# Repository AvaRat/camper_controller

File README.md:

# Camper Controller

## Overview
The project aims to create a usable system that can be mounted in a campervan, trailer, 4x4 overland vehicle or even small boat. It might be usefull in setups where 12V installation is present.
High level system design is presented in [system design doc](<CamperVan Control Unit system design.pdf>) .

## How to interpret this repo
Project contains electronic parts as well as control logic and user interface source codes. I decided to keep everything in one repo as all parts are pretty much dependent on each other, and with this being one-person project keeping all parts in one place make perfect sense to me.

Please see [design decisions.md](design_decisions.md) for details regarding some of the decision made.

## Roadmap
One of the gratest inspirations for me regarding how to organise things is the Opulo project: [opulo](https://github.com/opulo-inc/lumenpnp/tree/main) I'm still far away from it, but that's something I'm aiming for with respect to project structure and organisation.

Ideally I would like to use github pipelines to create BOM from PCB design files. Also somehow linking pin assignment from Kicad into C code would be great. 

Besides, the project is still in the early phase and requires some time to bring it to working prototype phase.

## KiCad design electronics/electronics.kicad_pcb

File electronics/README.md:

# Electronics for Camper Controller

TODO

image

short description

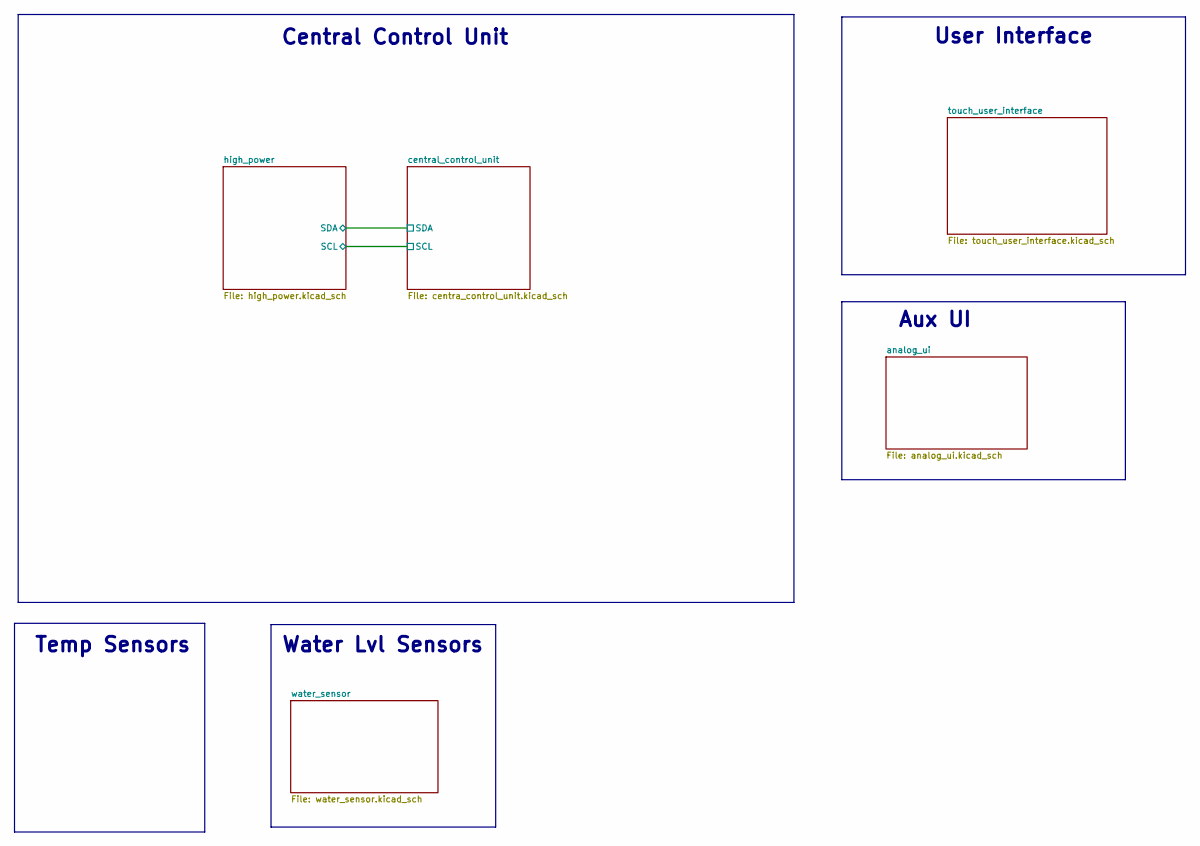
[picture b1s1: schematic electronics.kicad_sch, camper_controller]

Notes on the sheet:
User Interface
Central Control Unit
Temp Sensors
Water Lvl Sensors
Aux UI

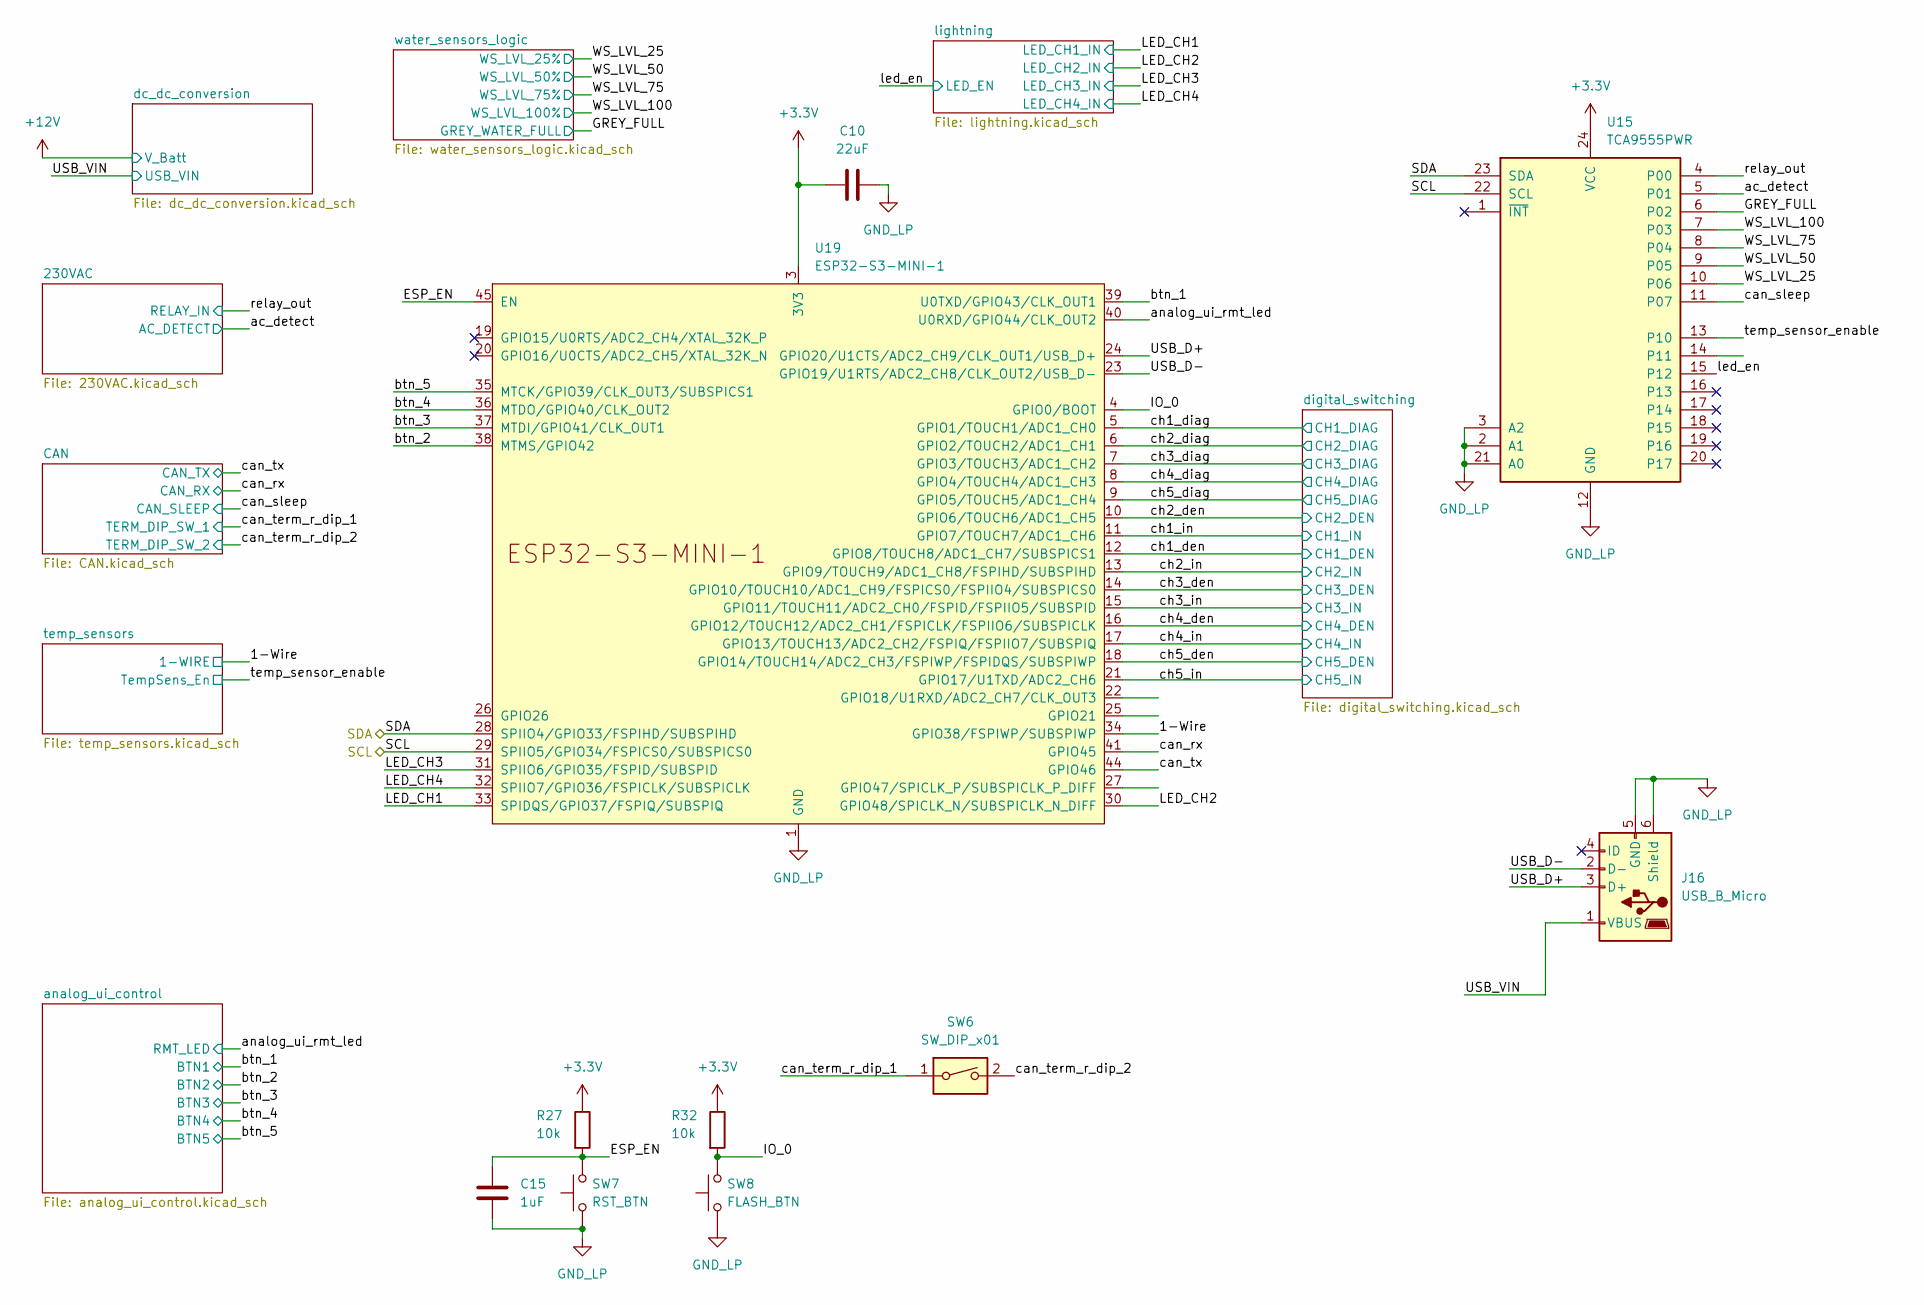
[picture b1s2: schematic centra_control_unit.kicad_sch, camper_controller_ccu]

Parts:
C10: 22uF; C_0805_2012Metric
C15: 1uF; C_0805_2012Metric
J16: USB_B_Micro; USB_Micro-B_Wuerth_614105150721_Vertical; LCSC C2926997
R27, R32: 10k; R_0805_2012Metric
SW6: SW_DIP_x01; PinHeader_1x02_P1.00mm_Vertical
SW7: RST_BTN; SW_PUSH_6mm_H4.3mm
SW8: FLASH_BTN; SW_PUSH_6mm_H4.3mm
U15: TCA9555PWR; TSSOP-24_4.4x7.8mm_P0.65mm; LCSC C465732
U19: ESP32-S3-MINI-1; ESP32-S3-MINI-1U

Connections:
+3.3V: C10.2, R27.1, R32.1, U15.24 (VCC), U19.3 (3V3); also elsewhere on the board
/central_control_unit/1-Wire: U19.34 (GPIO38/FSPIWP/SUBSPIWP); also elsewhere on the board
/central_control_unit/ESP_EN: C15.1, R27.2, SW7.2, U19.45 (EN)
/central_control_unit/GREY_FULL: U15.6 (P02); also elsewhere on the board
/central_control_unit/IO_0: R32.2, SW8.2, U19.4 (GPIO0/BOOT)
/central_control_unit/LED_CH1: U19.33 (SPIDQS/GPIO37/FSPIQ/SUBSPIQ); also elsewhere on the board
/central_control_unit/LED_CH2: U19.30 (GPIO48/SPICLK_N/SUBSPICLK_N_DIFF); also elsewhere on the board
/central_control_unit/LED_CH3: U19.31 (SPIIO6/GPIO35/FSPID/SUBSPID); also elsewhere on the board
/central_control_unit/LED_CH4: U19.32 (SPIIO7/GPIO36/FSPICLK/SUBSPICLK); also elsewhere on the board
/central_control_unit/SCL: U15.22 (SCL), U19.29 (SPIIO5/GPIO34/FSPICS0/SUBSPICS0); also elsewhere on the board
/central_control_unit/SDA: U15.23 (SDA), U19.28 (SPIIO4/GPIO33/FSPIHD/SUBSPIHD); also elsewhere on the board
/central_control_unit/USB_D+: J16.3 (D+), U19.24 (GPIO20/U1CTS/ADC2_CH9/CLK_OUT1/USB_D+)
/central_control_unit/USB_D-: J16.2 (D-), U19.23 (GPIO19/U1RTS/ADC2_CH8/CLK_OUT2/USB_D-)
/central_control_unit/USB_VIN: J16.1 (VBUS); also elsewhere on the board
/central_control_unit/WS_LVL_25: U15.10 (P06); also elsewhere on the board
/central_control_unit/WS_LVL_50: U15.9 (P05); also elsewhere on the board
/central_control_unit/WS_LVL_75: U15.8 (P04); also elsewhere on the board
/central_control_unit/WS_LVL_100: U15.7 (P03); also elsewhere on the board
/central_control_unit/ac_detect: U15.5 (P01); also elsewhere on the board
/central_control_unit/analog_ui_rmt_led: U19.40 (U0RXD/GPIO44/CLK_OUT2); also elsewhere on the board
/central_control_unit/btn_1: U19.39 (U0TXD/GPIO43/CLK_OUT1); also elsewhere on the board
/central_control_unit/btn_2: U19.38 (MTMS/GPIO42); also elsewhere on the board
/central_control_unit/btn_3: U19.37 (MTDI/GPIO41/CLK_OUT1); also elsewhere on the board
/central_control_unit/btn_4: U19.36 (MTDO/GPIO40/CLK_OUT2); also elsewhere on the board
/central_control_unit/btn_5: U19.35 (MTCK/GPIO39/CLK_OUT3/SUBSPICS1); also elsewhere on the board
/central_control_unit/can_rx: U19.41 (GPIO45); also elsewhere on the board
/central_control_unit/can_sleep: U15.11 (P07); also elsewhere on the board
/central_control_unit/can_term_r_dip_1: SW6.1; also elsewhere on the board
/central_control_unit/can_term_r_dip_2: SW6.2; also elsewhere on the board
/central_control_unit/can_tx: U19.44 (GPIO46); also elsewhere on the board
/central_control_unit/ch1_den: U19.12 (GPIO8/TOUCH8/ADC1_CH7/SUBSPICS1); also elsewhere on the board
/central_control_unit/ch1_diag: U19.5 (GPIO1/TOUCH1/ADC1_CH0); also elsewhere on the board
/central_control_unit/ch1_in: U19.11 (GPIO7/TOUCH7/ADC1_CH6); also elsewhere on the board
/central_control_unit/ch2_den: U19.10 (GPIO6/TOUCH6/ADC1_CH5); also elsewhere on the board
/central_control_unit/ch2_diag: U19.6 (GPIO2/TOUCH2/ADC1_CH1); also elsewhere on the board
/central_control_unit/ch2_in: U19.13 (GPIO9/TOUCH9/ADC1_CH8/FSPIHD/SUBSPIHD); also elsewhere on the board
/central_control_unit/ch3_den: U19.14 (GPIO10/TOUCH10/ADC1_CH9/FSPICS0/FSPIIO4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); also elsewhere on the board
/central_control_unit/ch3_diag: U19.7 (GPIO3/TOUCH3/ADC1_CH2); also elsewhere on the board
/central_control_unit/ch3_in: U19.15 (GPIO11/TOUCH11/ADC2_CH0/FSPID/FSPIIO5/S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); also elsewhere on the board
/central_control_unit/ch4_den: U19.16 (GPIO12/TOUCH12/ADC2_CH1/FSPICLK/FSPIIO6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); also elsewhere on the board
/central_control_unit/ch4_diag: U19.8 (GPIO4/TOUCH4/ADC1_CH3); also elsewhere on the board
/central_control_unit/ch4_in: U19.17 (GPIO13/TOUCH13/ADC2_CH2/FSPIQ/FSPIIO7/S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); also elsewhere on the board
/central_control_unit/ch5_den: U19.18 (GPIO14/TOUCH14/ADC2_CH3/FSPIWP/FSPIDQS/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); also elsewhere on the board
/central_control_unit/ch5_diag: U19.9 (GPIO5/TOUCH5/ADC1_CH4); also elsewhere on the board
/central_control_unit/digital_switching/CH5_IN: U19.21 (GPIO17/U1TXD/ADC2_CH6); also elsewhere on the board
/central_control_unit/led_en: U15.15 (P12); also elsewhere on the board
/central_control_unit/relay_out: U15.4 (P00); also elsewhere on the board
/central_control_unit/temp_sensor_enable: U15.13 (P10); also elsewhere on the board
GND_LP: C10.1, C15.2, J16.5 (GND), J16.6 (Shield), SW7.1, SW8.1, U15.2 (A1), U15.3 (A2), U15.12 (GND), U15.21 (A0), U19.1 (GND), U19.2 (GND), U19.42 (GND), U19.43 (GND), U19.46 (GND), U19.47 (GND), U19.48 (GND), U19.49 (GND), U19.50 (GND), U19.51 (GND), U19.52 (GND), U19.53 (GND), U19.54 (GND), U19.55 (GND), U19.56 (GND), U19.57 (GND), U19.58 (GND), U19.59 (GND), U19.60 (GND), U19.61 (GND), U19.62 (GND), U19.63 (GND), U19.64 (GND), U19.65 (GND); also elsewhere on the board

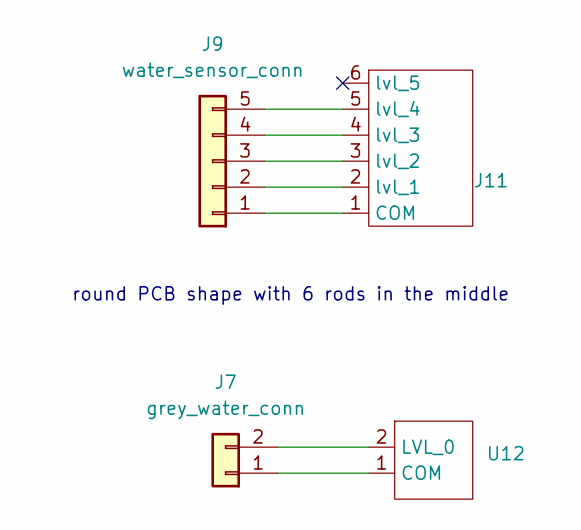
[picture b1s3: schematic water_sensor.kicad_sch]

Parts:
J7: grey_water_conn; Samtec_HPM-02-01-x-S_Straight_1x02_Pitch5.08mm
J9: water_sensor_conn; TerminalBlock_Xinya_XY308-2.54-5P_1x05_P2.54mm_Horizontal
J11: water_sensor_rods
U12: 2_water_sensor_rods

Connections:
unnamed: J7.1, U12.1 (COM)
unnamed: J7.2, U12.2 (LVL_0)
unnamed: J9.1, J11.1 (COM)
unnamed: J9.2, J11.2 (lvl_1)
unnamed: J9.3, J11.3 (lvl_2)
unnamed: J9.4, J11.4 (lvl_3)
unnamed: J9.5, J11.5 (lvl_4)

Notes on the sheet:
round PCB shape with 6 rods in the middle

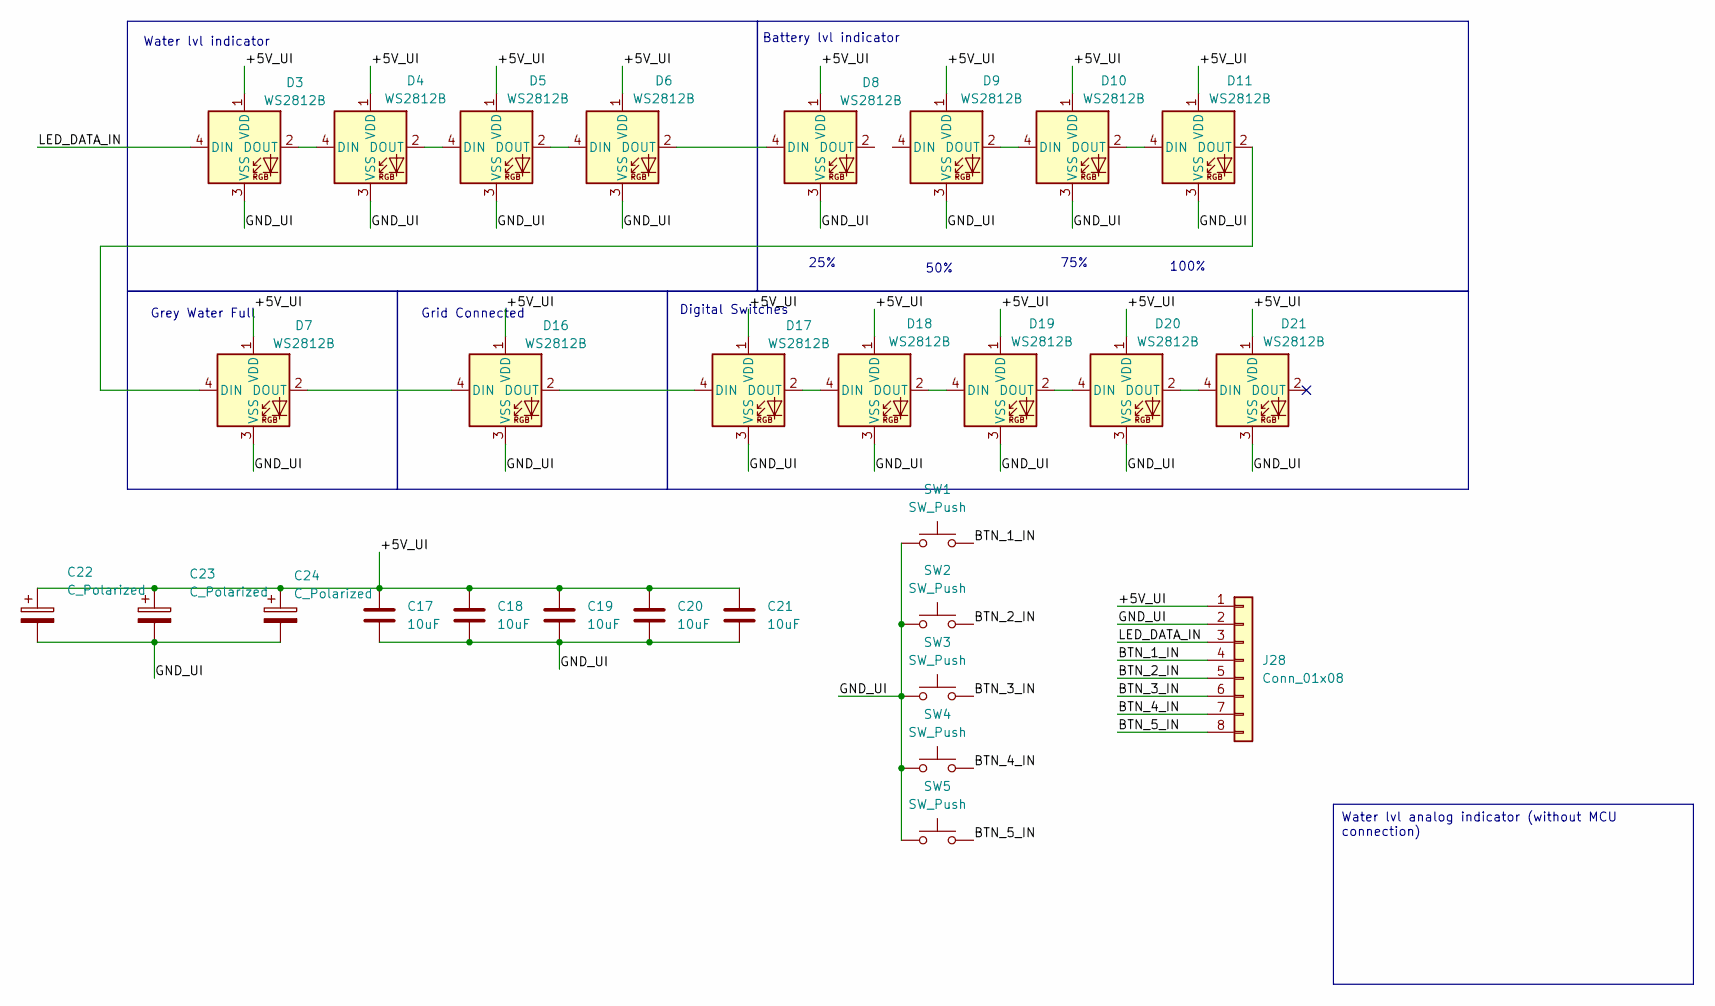
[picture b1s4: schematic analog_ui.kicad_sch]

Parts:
C17, C18, C19, C20, C21: 10uF; C_0805_2012Metric
C22, C23, C24: C_Polarized; CP_Radial_D5.0mm_P2.50mm
D3, D4, D5, D6, D7, D8, D9, D10, D11, D16, D17, D18, D19, D20, D21: WS2812B; LED_WS2812B_PLCC4_5.0x5.0mm_P3.2mm
J28: Conn_01x08; TerminalBlock_Xinya_XY308-2.54-8P_1x08_P2.54mm_Horizontal
SW1, SW2, SW3, SW4, SW5: SW_Push; button_12mm

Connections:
/analog_ui/+5V_UI: C17.1, C18.1, C19.1, C20.1, C21.1, C22.1, C23.1, C24.1, D3.1 (VDD), D4.1 (VDD), D5.1 (VDD), D6.1 (VDD), D7.1 (VDD), D8.1 (VDD), D9.1 (VDD), D10.1 (VDD), D11.1 (VDD), D16.1 (VDD), D17.1 (VDD), D18.1 (VDD), D19.1 (VDD), D20.1 (VDD), D21.1 (VDD), J28.1
/analog_ui/BTN_1_IN: J28.4, SW1.2
/analog_ui/BTN_2_IN: J28.5, SW2.2
/analog_ui/BTN_3_IN: J28.6, SW3.2
/analog_ui/BTN_4_IN: J28.7, SW4.2
/analog_ui/BTN_5_IN: J28.8, SW5.2
/analog_ui/GND_UI: C17.2, C18.2, C19.2, C20.2, C21.2, C22.2, C23.2, C24.2, D3.3 (VSS), D4.3 (VSS), D5.3 (VSS), D6.3 (VSS), D7.3 (VSS), D8.3 (VSS), D9.3 (VSS), D10.3 (VSS), D11.3 (VSS), D16.3 (VSS), D17.3 (VSS), D18.3 (VSS), D19.3 (VSS), D20.3 (VSS), D21.3 (VSS), J28.2, SW1.1, SW2.1, SW3.1, SW4.1, SW5.1
/analog_ui/LED_DATA_IN: D3.4 (DIN), J28.3
unnamed: D3.2 (DOUT), D4.4 (DIN)
unnamed: D4.2 (DOUT), D5.4 (DIN)
unnamed: D5.2 (DOUT), D6.4 (DIN)
unnamed: D6.2 (DOUT), D8.4 (DIN)
unnamed: D9.2 (DOUT), D10.4 (DIN)
unnamed: D10.2 (DOUT), D11.4 (DIN)
unnamed: D7.4 (DIN), D11.2 (DOUT)
unnamed: D7.2 (DOUT), D16.4 (DIN)
unnamed: D16.2 (DOUT), D17.4 (DIN)
unnamed: D17.2 (DOUT), D18.4 (DIN)
unnamed: D18.2 (DOUT), D19.4 (DIN)
unnamed: D19.2 (DOUT), D20.4 (DIN)
unnamed: D20.2 (DOUT), D21.4 (DIN)

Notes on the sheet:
Water lvl analog indicator (without MCU connection)
Grid Connected
75%
Water lvl indicator
Battery lvl indicator
25%
50%
Grey Water Full
Digital Switches
100%

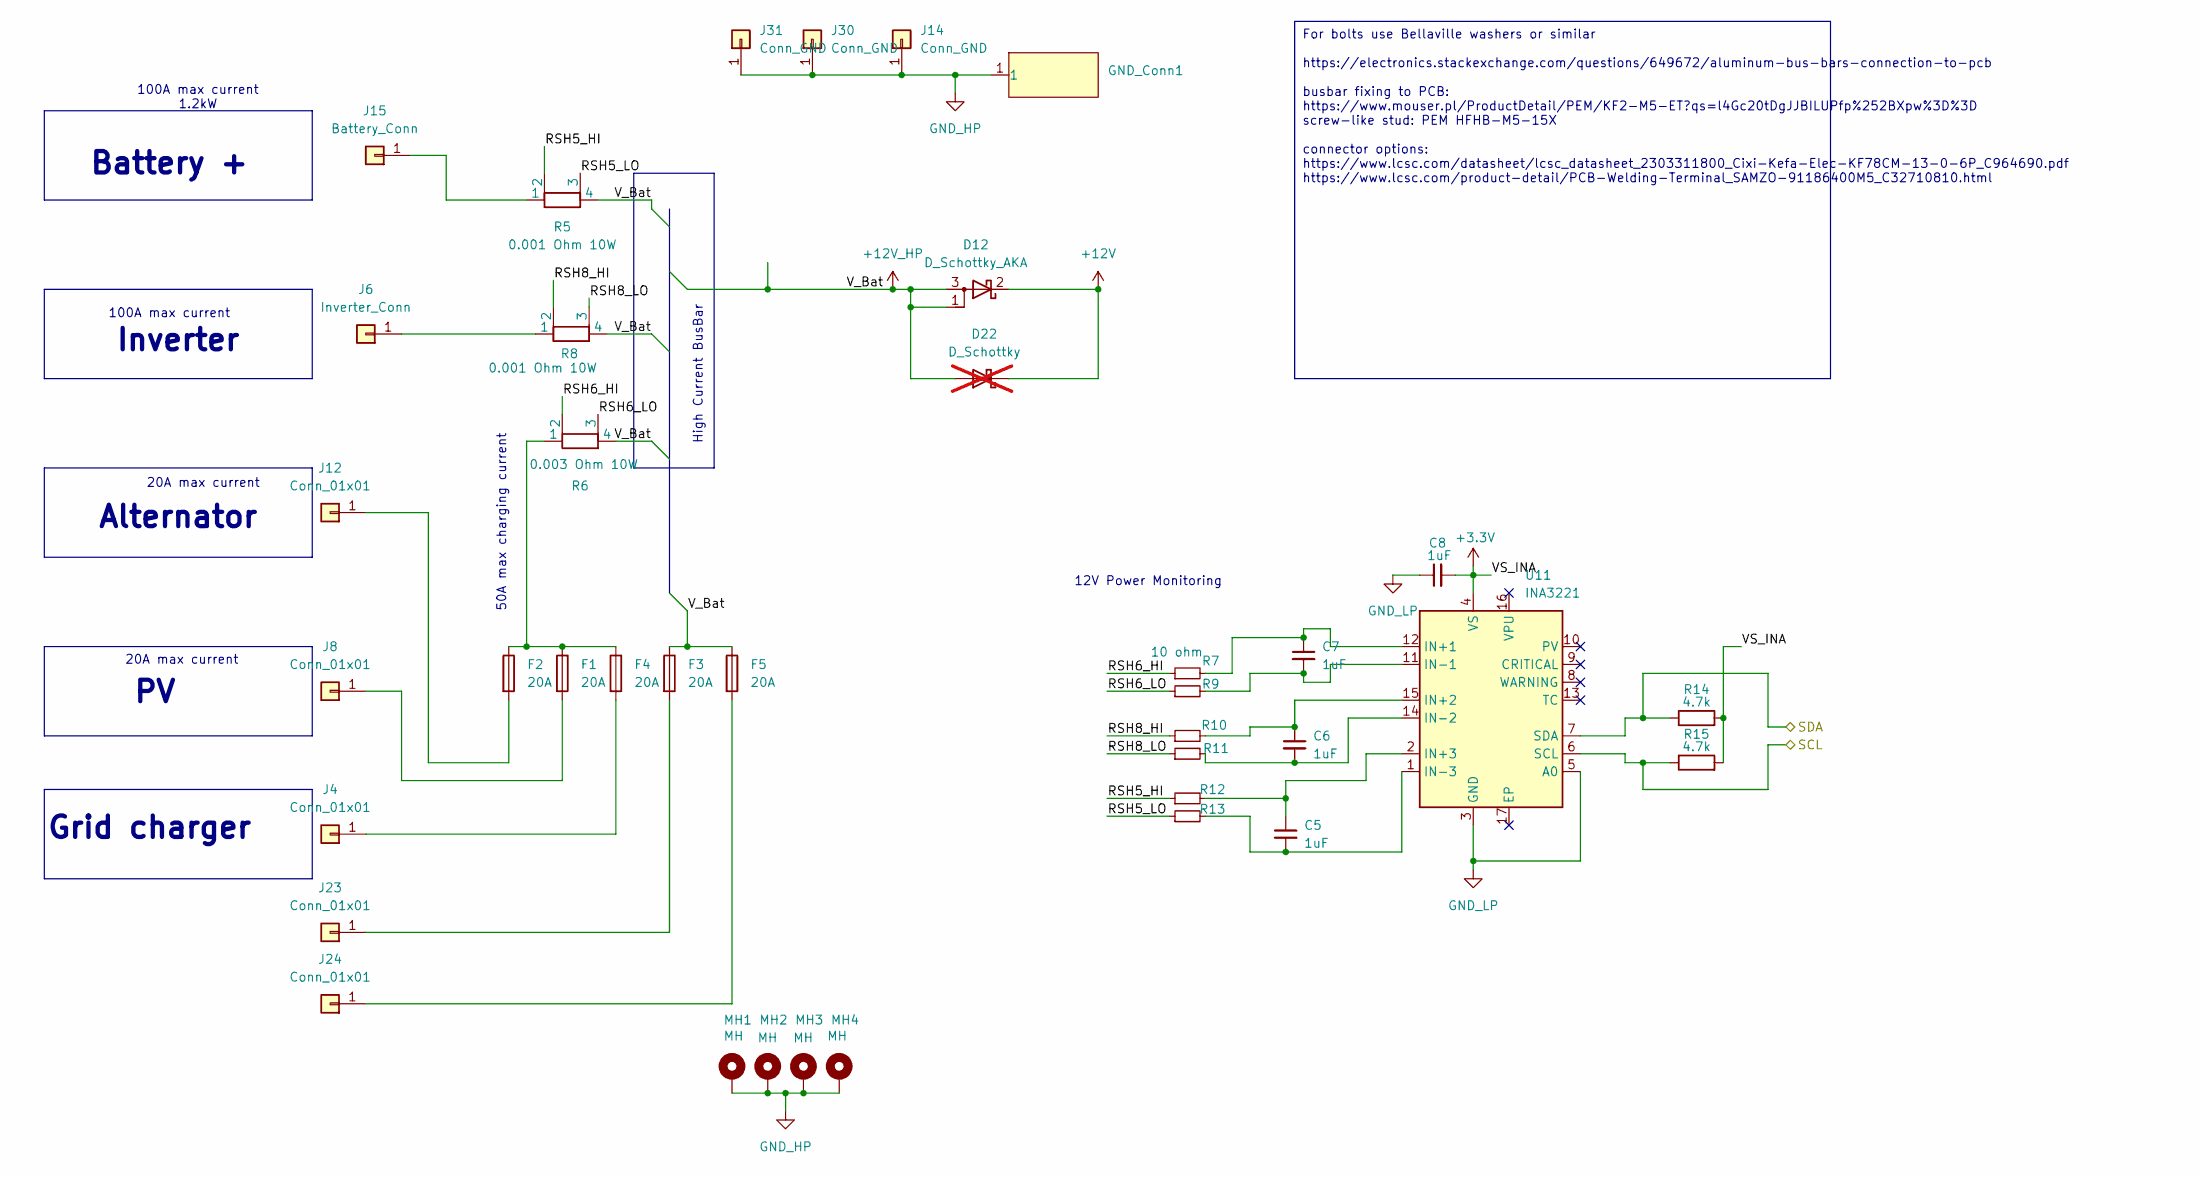
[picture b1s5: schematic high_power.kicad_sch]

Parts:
C5, C6, C7, C8: 1uF; C_0805_2012Metric
D12: D_Schottky_AKA; TO-252-2
D22: D_Schottky; D_DO-15_P3.81mm_Vertical_AnodeUp; not fitted
F1, F3, F5: 20A; ATO_fuse_holder; LCSC_part C2935871
F2: 20A; ATO_fuse_holder
F4: 20A; ATO_fuse_holder; lcsc_part C2935871
GND_Conn1: small_busbar-15mm
J4, J8, J12, J23, J24: Conn_01x01; keystone_m3_screw_terminal_vertical
J6: Inverter_Conn; keystone_m3_screw_terminal_vertical
J14, J30, J31: Conn_GND; keystone_m3_screw_terminal_vertical
J15: Battery_Conn; keystone_m3_screw_terminal_vertical
MH1, MH2, MH3, MH4: MH; MountingHole_3.2mm_M3_ISO7380_Pad_TopBottom
R5, R8: 0.001 Ohm 10W; MSRSF_shunt_resistor; Mouser_Nr 754-MSRSF5930P1L0F2P
R6: 0.003 Ohm 10W; MSRSF_shunt_resistor; Mouser_Nr 754-MSRSF5930P1L0F2P
R7, R9, R10, R11, R12, R13: 10 ohm; R_0805_2012Metric
R14, R15: 4.7k; R_0805_2012Metric
U11: INA3221; Texas_RGV0016A_VQFN-16-1EP_4x4mm_P0.65mm_EP2.1x2.1mm

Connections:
+3.3V: C8.2, R14.2, R15.2, U11.4 (VS); also elsewhere on the board
+12V: D12.2 (K), D22.1 (K); also elsewhere on the board
+12V_HP: D12.1 (A), D12.3 (A), D22.2 (A), F3.1, F5.1, R5.4, R6.4, R8.4; also elsewhere on the board
/central_control_unit/SCL: R15.1, U11.6 (SCL); also elsewhere on the board
/central_control_unit/SDA: R14.1, U11.7 (SDA); also elsewhere on the board
/high_power/RSH5_HI: R5.2, R12.1
/high_power/RSH5_LO: R5.3, R13.1
/high_power/RSH6_HI: R6.2, R7.1
/high_power/RSH6_LO: R6.3, R9.1
/high_power/RSH8_HI: R8.2, R10.1
/high_power/RSH8_LO: R8.3, R11.1
GND_HP: GND_Conn1.1, J14.1, J30.1, J31.1, MH1.1, MH2.1, MH3.1, MH4.1; also elsewhere on the board
GND_LP: C8.1, U11.3 (GND), U11.5 (A0); also elsewhere on the board
unnamed: F1.1, F2.1, F4.1, R6.1
unnamed: F4.2, J4.1
unnamed: J6.1, R8.1
unnamed: F1.2, J8.1
unnamed: F2.2, J12.1
unnamed: J15.1, R5.1
unnamed: F3.2, J23.1
unnamed: F5.2, J24.1
unnamed: C7.1, R7.2, U11.12 (IN+1)
unnamed: C6.1, R10.2, U11.15 (IN+2)
unnamed: C5.1, R12.2, U11.2 (IN+3)
unnamed: C7.2, R9.2, U11.11 (IN-1)
unnamed: C6.2, R11.2, U11.14 (IN-2)
unnamed: C5.2, R13.2, U11.1 (IN-3)

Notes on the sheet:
For bolts use Bellaville washers or similar https://electronics.stackexchange.com/questions/649672/aluminum-bus-bars-connection-to-pcb busbar fixing to PCB: https://www.mouser.pl/ProductDetail/PEM/KF2-M5-ET?qs=l4Gc20tDgJJBILUPfp%252BXpw%3D%3D screw-like stud: PEM HFHB-M5-15X connector options: http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
100A max current
50A max charging current
100A max current 1.2kW
Inverter
Battery +
20A max current
Alternator
12V Power Monitoring
Grid charger
High Current BusBar

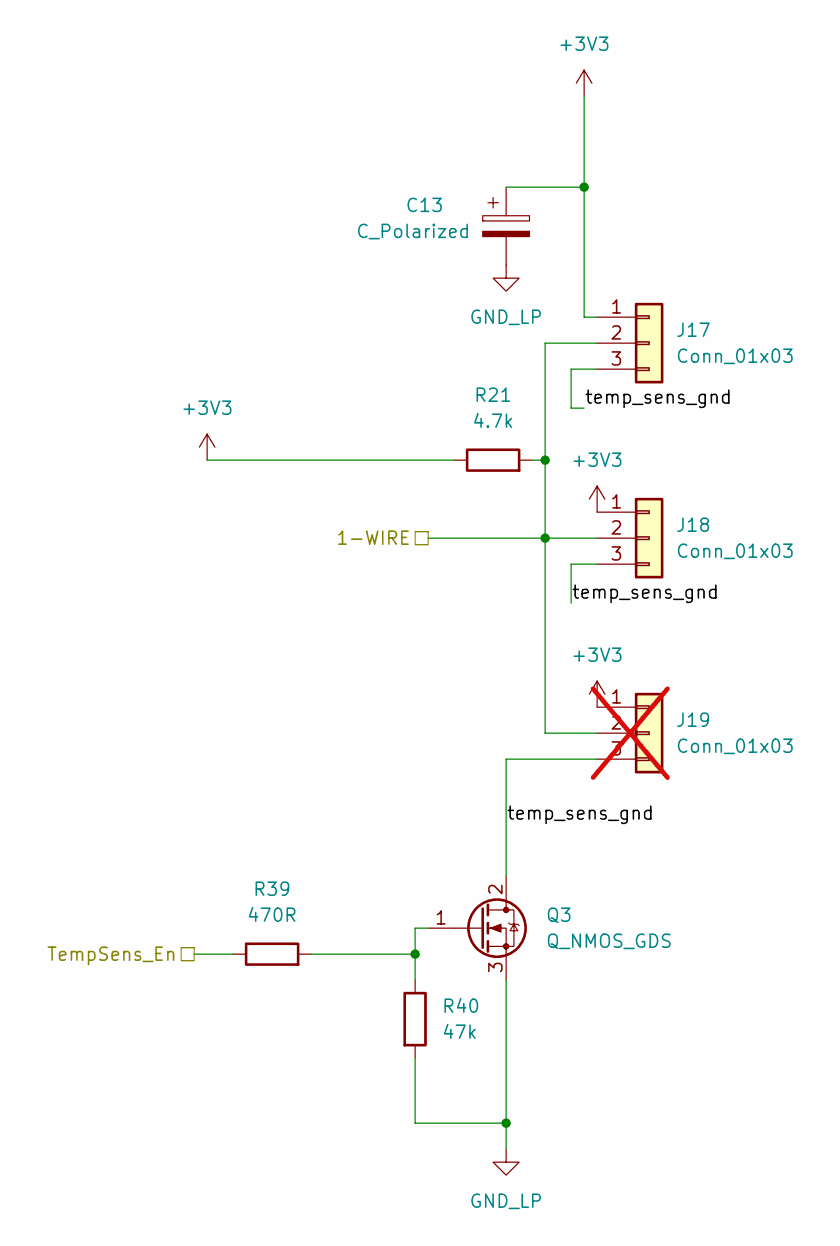
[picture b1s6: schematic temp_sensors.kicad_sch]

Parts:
C13: C_Polarized; CP_Radial_D5.0mm_P2.50mm
J17, J18: Conn_01x03; TerminalBlock_Xinya_XY308-2.54-3P_1x03_P2.54mm_Horizontal
J19: Conn_01x03; TerminalBlock_Xinya_XY308-2.54-3P_1x03_P2.54mm_Horizontal; not fitted
Q3: Q_NMOS_GDS; SOT-23; Mrf_part AO3400-HXY; JLC C4748804
R21: 4.7k; R_0805_2012Metric
R39: 470R; R_0805_2012Metric
R40: 47k; R_0805_2012Metric

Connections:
/central_control_unit/1-Wire: J17.2, J18.2, J19.2, R21.2; also elsewhere on the board
/central_control_unit/temp_sensor_enable: R39.1; also elsewhere on the board
/central_control_unit/temp_sensors/temp_sens_gnd: J17.3, J18.3, J19.3, Q3.2 (D)
GND_LP: C13.2, Q3.3 (S), R40.2; also elsewhere on the board
unnamed: Q3.1 (G), R39.2, R40.1

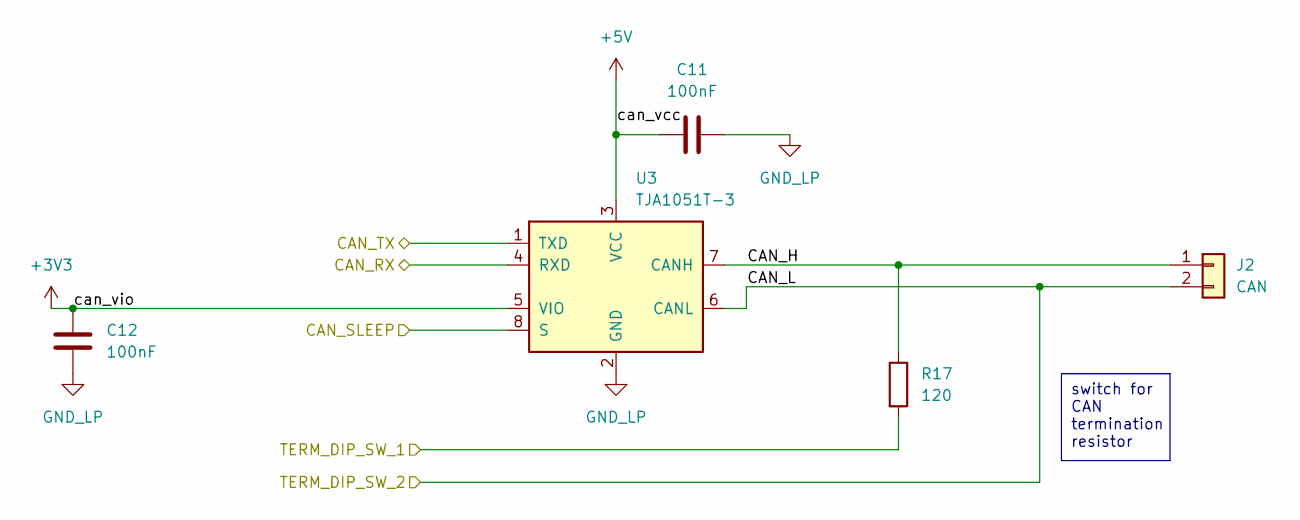
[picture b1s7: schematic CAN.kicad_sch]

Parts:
C11, C12: 100nF; C_0805_2012Metric
J2: CAN; TerminalBlock_Xinya_XY308-2.54-2P_1x02_P2.54mm_Horizontal
R17: 120; R_0805_2012Metric
U3: TJA1051T-3; SOIC-8_3.9x4.9mm_P1.27mm

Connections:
+5V: C11.1, U3.3 (VCC); also elsewhere on the board
/central_control_unit/CAN/CAN_H: J2.1, R17.1, U3.7 (CANH)
/central_control_unit/CAN/can_vio: C12.1, U3.5 (VIO)
/central_control_unit/can_rx: U3.4 (RXD); also elsewhere on the board
/central_control_unit/can_sleep: U3.8 (S); also elsewhere on the board
/central_control_unit/can_term_r_dip_1: R17.2; also elsewhere on the board
/central_control_unit/can_term_r_dip_2: J2.2, U3.6 (CANL); also elsewhere on the board
/central_control_unit/can_tx: U3.1 (TXD); also elsewhere on the board
GND_LP: C11.2, C12.2, U3.2 (GND); also elsewhere on the board

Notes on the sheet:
switch for CAN termination resistor

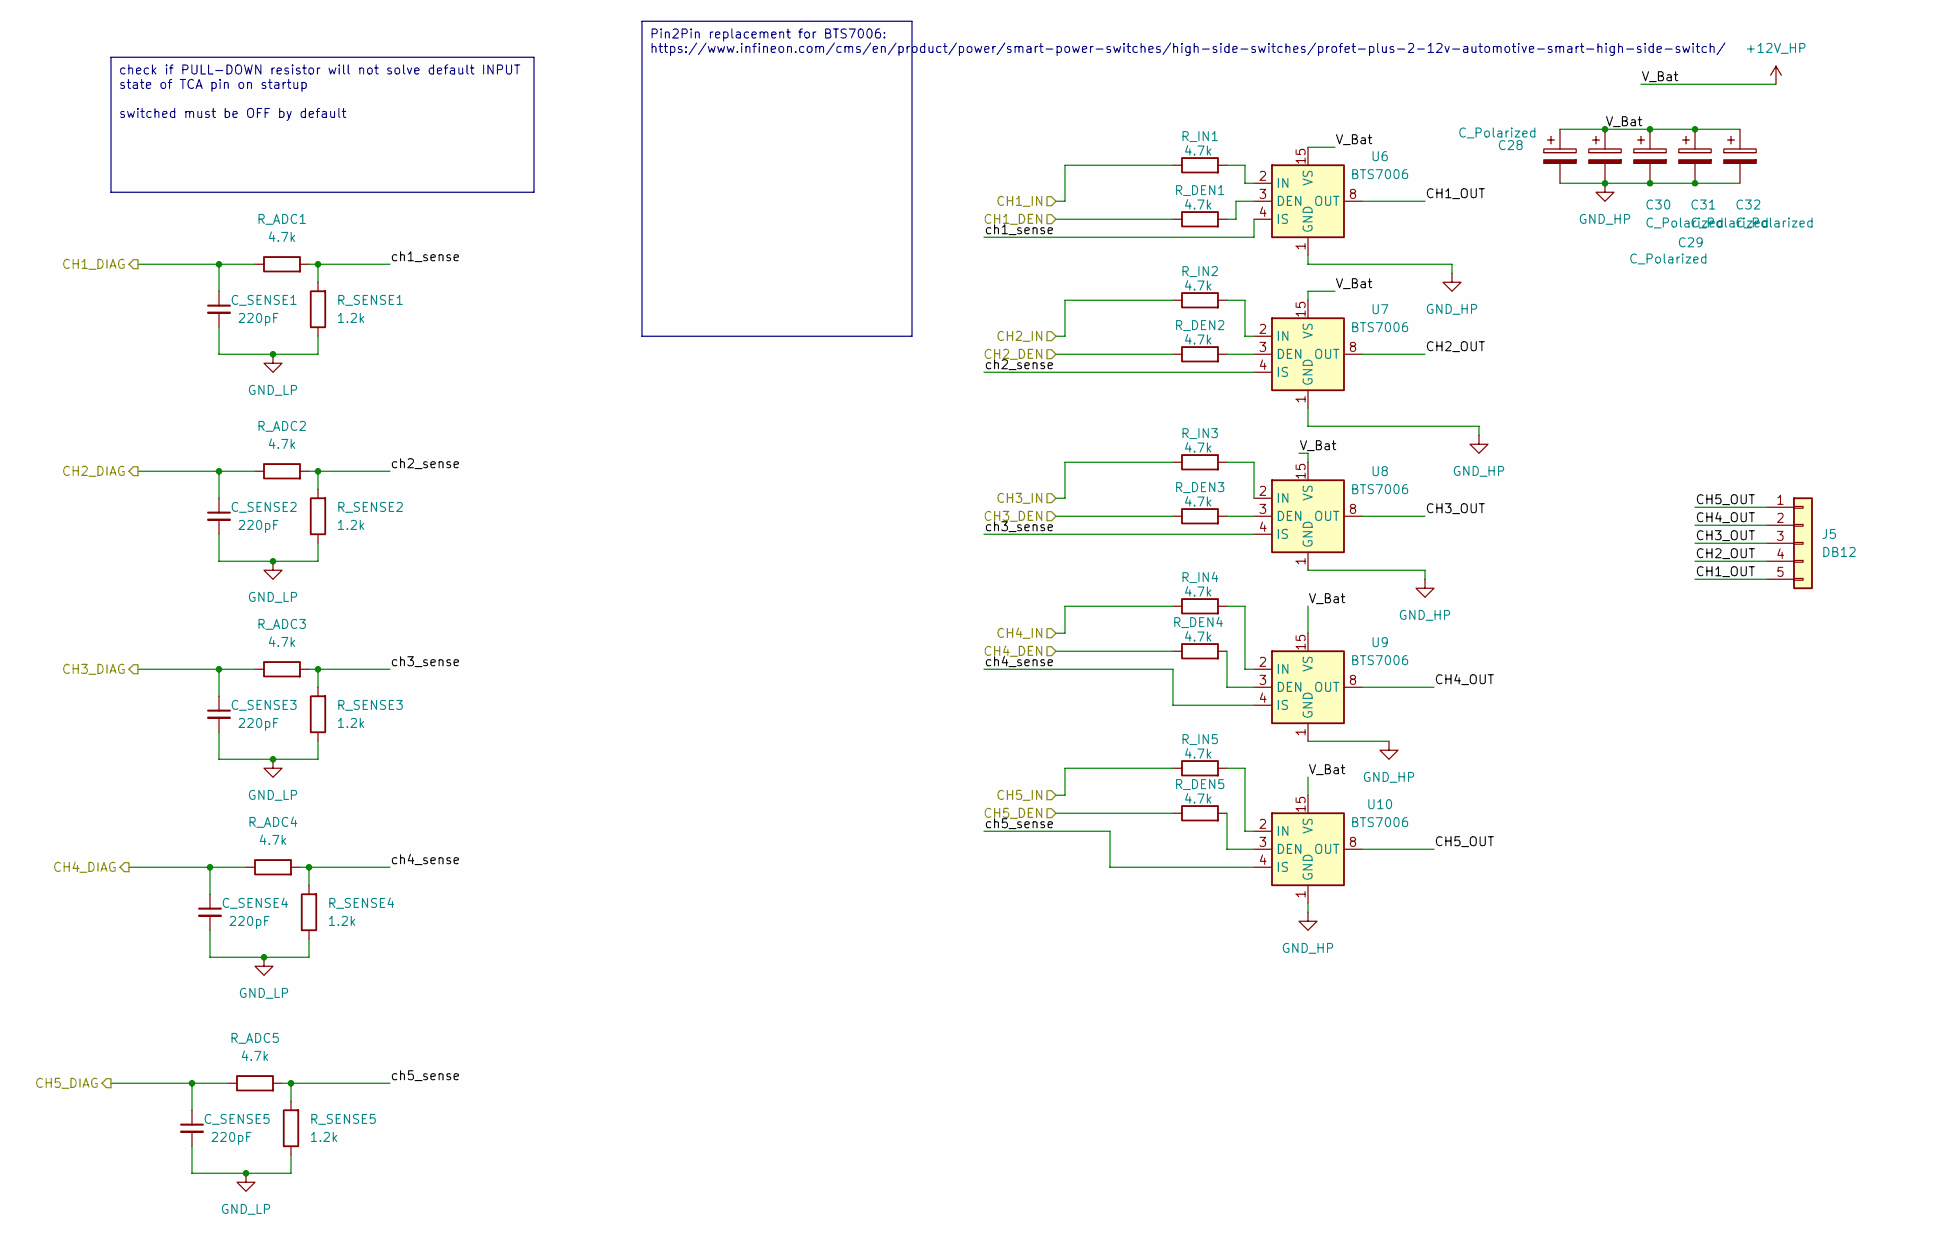
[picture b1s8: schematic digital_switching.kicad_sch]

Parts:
C28, C29, C30, C31, C32: C_Polarized; CP_Radial_D5.0mm_P2.50mm
C_SENSE1, C_SENSE2, C_SENSE3, C_SENSE4: 220pF; C_0805_2012Metric
C_SENSE5: 220pF; C_1210_3225Metric_Pad1.33x2.70mm_HandSolder
J5: DB12; 5p_terminal_DB12; LCSCc C2927513
R_ADC1, R_ADC2, R_ADC3, R_ADC4, R_ADC5: 4.7k; R_0805_2012Metric
R_DEN1, R_DEN2, R_DEN3, R_DEN4, R_DEN5: 4.7k; R_0805_2012Metric
R_IN1, R_IN2, R_IN3, R_IN4, R_IN5: 4.7k; R_0805_2012Metric
R_SENSE1, R_SENSE2, R_SENSE3, R_SENSE4, R_SENSE5: 1.2k; R_0805_2012Metric
U6: BTS7006; Infineon_PG-TSDSO-14-22; Mfr Part BTS7006-1EPP; Mouser 726-BTS70061EPPXUMA1
U7, U8, U9, U10: BTS7006; Infineon_PG-TSDSO-14-22

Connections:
+12V_HP: C28.1, C29.1, C30.1, C31.1, C32.1, U6.15 (VS), U7.15 (VS), U8.15 (VS), U9.15 (VS), U10.15 (VS); also elsewhere on the board
/central_control_unit/ch1_den: R_DEN1.1; also elsewhere on the board
/central_control_unit/ch1_diag: C_SENSE1.1, R_ADC1.1; also elsewhere on the board
/central_control_unit/ch1_in: R_IN1.1; also elsewhere on the board
/central_control_unit/ch2_den: R_DEN2.1; also elsewhere on the board
/central_control_unit/ch2_diag: C_SENSE2.1, R_ADC2.1; also elsewhere on the board
/central_control_unit/ch2_in: R_IN2.1; also elsewhere on the board
/central_control_unit/ch3_den: R_DEN3.1; also elsewhere on the board
/central_control_unit/ch3_diag: C_SENSE3.1, R_ADC3.1; also elsewhere on the board
/central_control_unit/ch3_in: R_IN3.1; also elsewhere on the board
/central_control_unit/ch4_den: R_DEN4.1; also elsewhere on the board
/central_control_unit/ch4_diag: C_SENSE4.1, R_ADC4.1; also elsewhere on the board
/central_control_unit/ch4_in: R_IN4.1; also elsewhere on the board
/central_control_unit/ch5_den: R_DEN5.1; also elsewhere on the board
/central_control_unit/ch5_diag: C_SENSE5.1, R_ADC5.1; also elsewhere on the board
/central_control_unit/digital_switching/CH1_OUT: J5.5, U6.8 (OUT), U6.9 (OUT), U6.10 (OUT), U6.12 (OUT), U6.13 (OUT), U6.14 (OUT)
/central_control_unit/digital_switching/CH2_OUT: J5.4, U7.8 (OUT), U7.9 (OUT), U7.10 (OUT), U7.12 (OUT), U7.13 (OUT), U7.14 (OUT)
/central_control_unit/digital_switching/CH3_OUT: J5.3, U8.8 (OUT), U8.9 (OUT), U8.10 (OUT), U8.12 (OUT), U8.13 (OUT), U8.14 (OUT)
/central_control_unit/digital_switching/CH4_OUT: J5.2, U9.8 (OUT), U9.9 (OUT), U9.10 (OUT), U9.12 (OUT), U9.13 (OUT), U9.14 (OUT)
/central_control_unit/digital_switching/CH5_IN: R_IN5.1; also elsewhere on the board
/central_control_unit/digital_switching/CH5_OUT: J5.1, U10.8 (OUT), U10.9 (OUT), U10.10 (OUT), U10.12 (OUT), U10.13 (OUT), U10.14 (OUT)
/central_control_unit/digital_switching/ch1_sense: R_ADC1.2, R_SENSE1.2, U6.4 (IS)
/central_control_unit/digital_switching/ch2_sense: R_ADC2.2, R_SENSE2.2, U7.4 (IS)
/central_control_unit/digital_switching/ch3_sense: R_ADC3.2, R_SENSE3.2, U8.4 (IS)
/central_control_unit/digital_switching/ch4_sense: R_ADC4.2, R_SENSE4.2, U9.4 (IS)
/central_control_unit/digital_switching/ch5_sense: R_ADC5.2, R_SENSE5.2, U10.4 (IS)
GND_HP: C28.2, C29.2, C30.2, C31.2, C32.2, U6.1 (GND), U7.1 (GND), U8.1 (GND), U9.1 (GND), U10.1 (GND); also elsewhere on the board
GND_LP: C_SENSE1.2, C_SENSE2.2, C_SENSE3.2, C_SENSE4.2, C_SENSE5.2, R_SENSE1.1, R_SENSE2.1, R_SENSE3.1, R_SENSE4.1, R_SENSE5.1; also elsewhere on the board
unnamed: R_DEN1.2, U6.3 (DEN)
unnamed: R_IN1.2, U6.2 (IN)
unnamed: R_DEN2.2, U7.3 (DEN)
unnamed: R_IN2.2, U7.2 (IN)
unnamed: R_DEN3.2, U8.3 (DEN)
unnamed: R_IN3.2, U8.2 (IN)
unnamed: R_DEN4.2, U9.3 (DEN)
unnamed: R_IN4.2, U9.2 (IN)
unnamed: R_DEN5.2, U10.3 (DEN)
unnamed: R_IN5.2, U10.2 (IN)

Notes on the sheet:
check if PULL-DOWN resistor will not solve default INPUT state of TCA pin on startup switched must be OFF by default
Pin2Pin replacement for BTS7006: https://www.infineon.com/cms/en/product/power/smart-power-switches/high-side-switches/profet-plus-2-12v-automotive-smart-high-side-switch/

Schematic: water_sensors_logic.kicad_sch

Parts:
J10: water_sensor_conn; TerminalBlock_Xinya_XY308-2.54-5P_1x05_P2.54mm_Horizontal
J13: Conn_01x02; TerminalBlock_Xinya_XY308-2.54-2P_1x02_P2.54mm_Horizontal
R16, R26: 100k; R_0805_2012Metric
R28, R29, R30, R31: 1M; R_0805_2012Metric
U5, U14: LM339_4ch; SOIC-14_3.9x8.7mm_P1.27mm; Mfr Part LM339DR; lcsc C7948

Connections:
/central_control_unit/GREY_FULL: U5.2 (OUT1); also elsewhere on the board
/central_control_unit/WS_LVL_25: U14.13 (OUT4); also elsewhere on the board
/central_control_unit/WS_LVL_50: U14.14 (OUT3); also elsewhere on the board
/central_control_unit/WS_LVL_75: U14.1 (OUT2); also elsewhere on the board
/central_control_unit/WS_LVL_100: U14.2 (OUT1); also elsewhere on the board
/central_control_unit/water_sensors_logic/grey_water_probe: J13.2, U5.4 (IN1-)
/central_control_unit/water_sensors_logic/probe_1: J10.5, R28.2, U14.4 (IN1-)
/central_control_unit/water_sensors_logic/probe_2: J10.4, R29.2, U14.6 (IN2-)
/central_control_unit/water_sensors_logic/probe_3: J10.3, R30.2, U14.8 (IN3-)
/central_control_unit/water_sensors_logic/probe_4: J10.2, R31.2, U14.10 (IN4-)
/central_control_unit/water_sensors_logic/ws_vref: R16.1, R26.2, U5.5 (IN1+), U14.5 (IN1+), U14.7 (IN2+), U14.9 (IN3+), U14.11 (IN4+)
GND_LP: J10.1, J13.1, R26.1, U5.12 (GND), U14.12 (GND); also elsewhere on the board

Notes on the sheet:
output is HIGH when probe NOT IN water output is LOW when probe IN water
